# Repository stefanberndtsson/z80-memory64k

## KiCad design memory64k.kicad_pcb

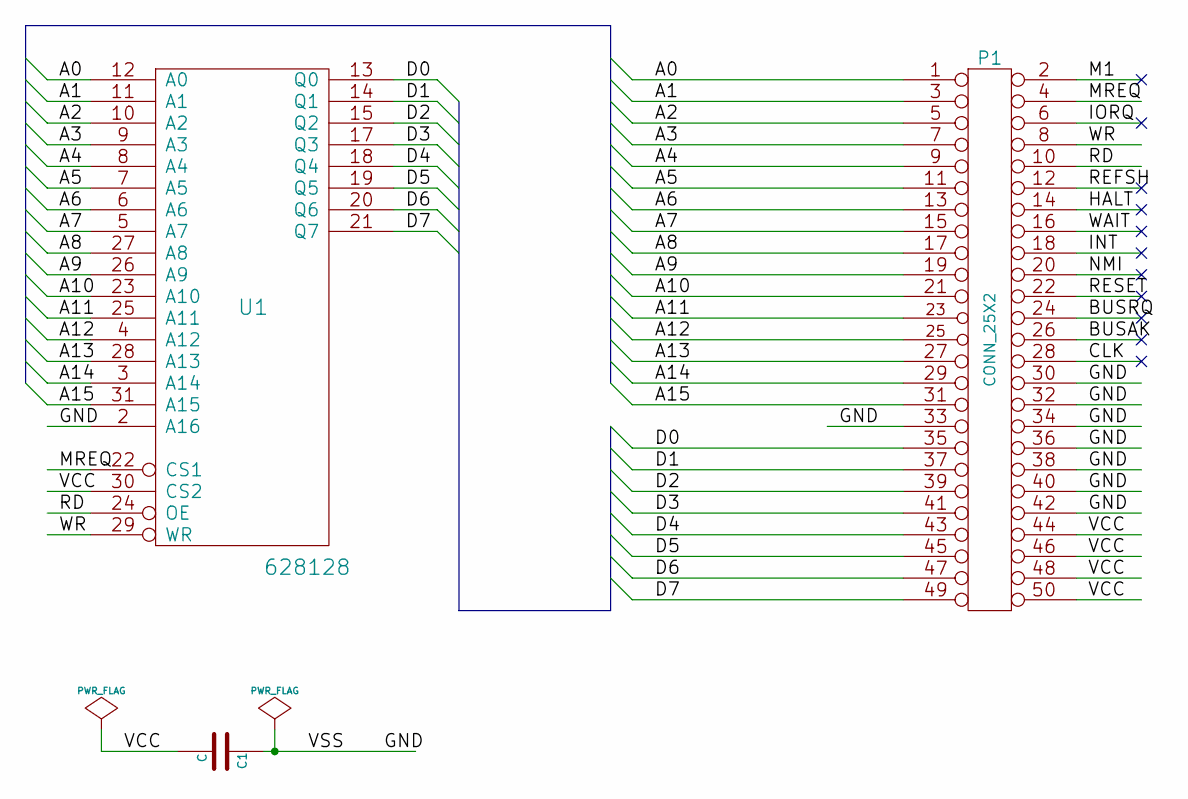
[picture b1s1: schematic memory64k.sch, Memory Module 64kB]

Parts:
C1: C; Capacitor3MMDiscRM2.5
P1: CONN_25X2; Socket_Strip_Straight_2x25
U1: 628128; DIP32-400_ELL

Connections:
/A0: P1.1, U1.12 (A0)
/A1: P1.3, U1.11 (A1)
/A2: P1.5, U1.10 (A2)
/A3: P1.7, U1.9 (A3)
/A4: P1.9, U1.8 (A4)
/A5: P1.11, U1.7 (A5)
/A6: P1.13, U1.6 (A6)
/A7: P1.15, U1.5 (A7)
/A8: P1.17, U1.27 (A8)
/A9: P1.19, U1.26 (A9)
/A10: P1.21, U1.23 (A10)
/A11: P1.23, U1.25 (A11)
/A12: P1.25, U1.4 (A12)
/A13: P1.27, U1.28 (A13)
/A14: P1.29, U1.3 (A14)
/A15: P1.31, U1.31 (A15)
/BUSAK: P1.26
/BUSRQ: P1.24
/CLK: P1.28
/D0: P1.35, U1.13 (Q0)
/D1: P1.37, U1.14 (Q1)
/D2: P1.39, U1.15 (Q2)
/D3: P1.41, U1.17 (Q3)
/D4: P1.43, U1.18 (Q4)
/D5: P1.45, U1.19 (Q5)
/D6: P1.47, U1.20 (Q6)
/D7: P1.49, U1.21 (Q7)
/HALT: P1.14
/INT: P1.18
/IORQ: P1.6
/M1: P1.2
/MREQ: P1.4, U1.22 (CS1)
/NMI: P1.20
/RD: P1.10, U1.24 (OE)
/REFSH: P1.12
/RESET: P1.22
/WAIT: P1.16
/WR: P1.8, U1.29 (WR)
GND: C1.1, P1.30, P1.32, P1.33, P1.34, P1.36, P1.38, P1.40, P1.42, U1.2 (A16), U1.16 (GND)
VCC: C1.2, P1.44, P1.46, P1.48, P1.50, U1.30 (CS2), U1.32 (VCC)

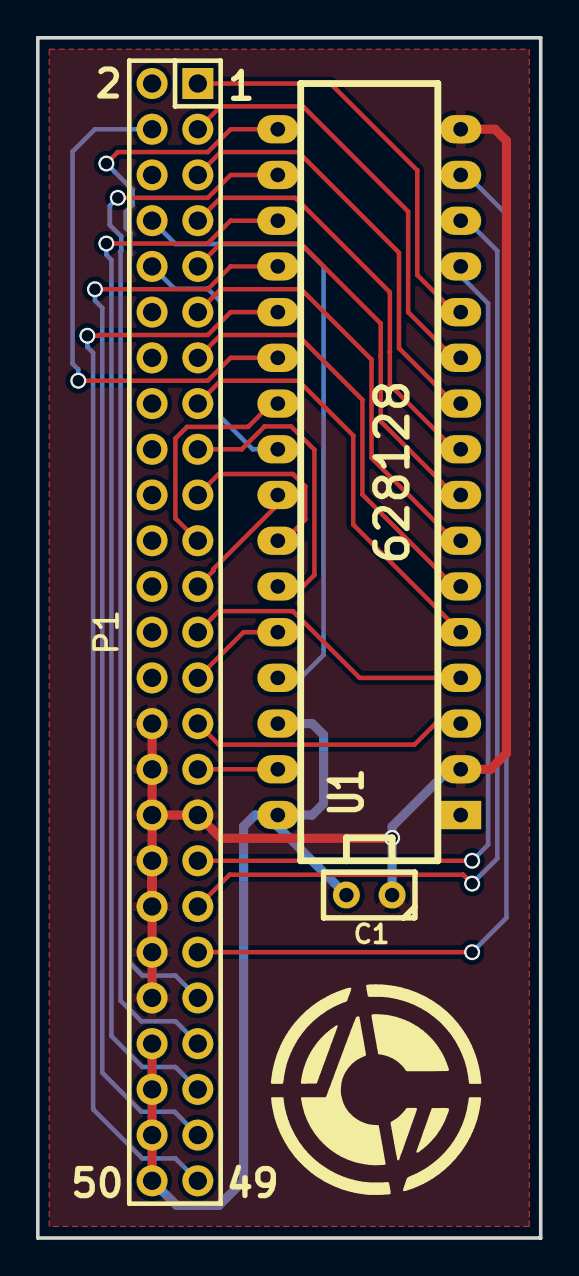
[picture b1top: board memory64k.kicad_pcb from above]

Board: 2 copper layers, 27.9 x 66.7 mm, 3 parts (0 on the bottom side), 29 nets.

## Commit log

2014-08-15 Initial
